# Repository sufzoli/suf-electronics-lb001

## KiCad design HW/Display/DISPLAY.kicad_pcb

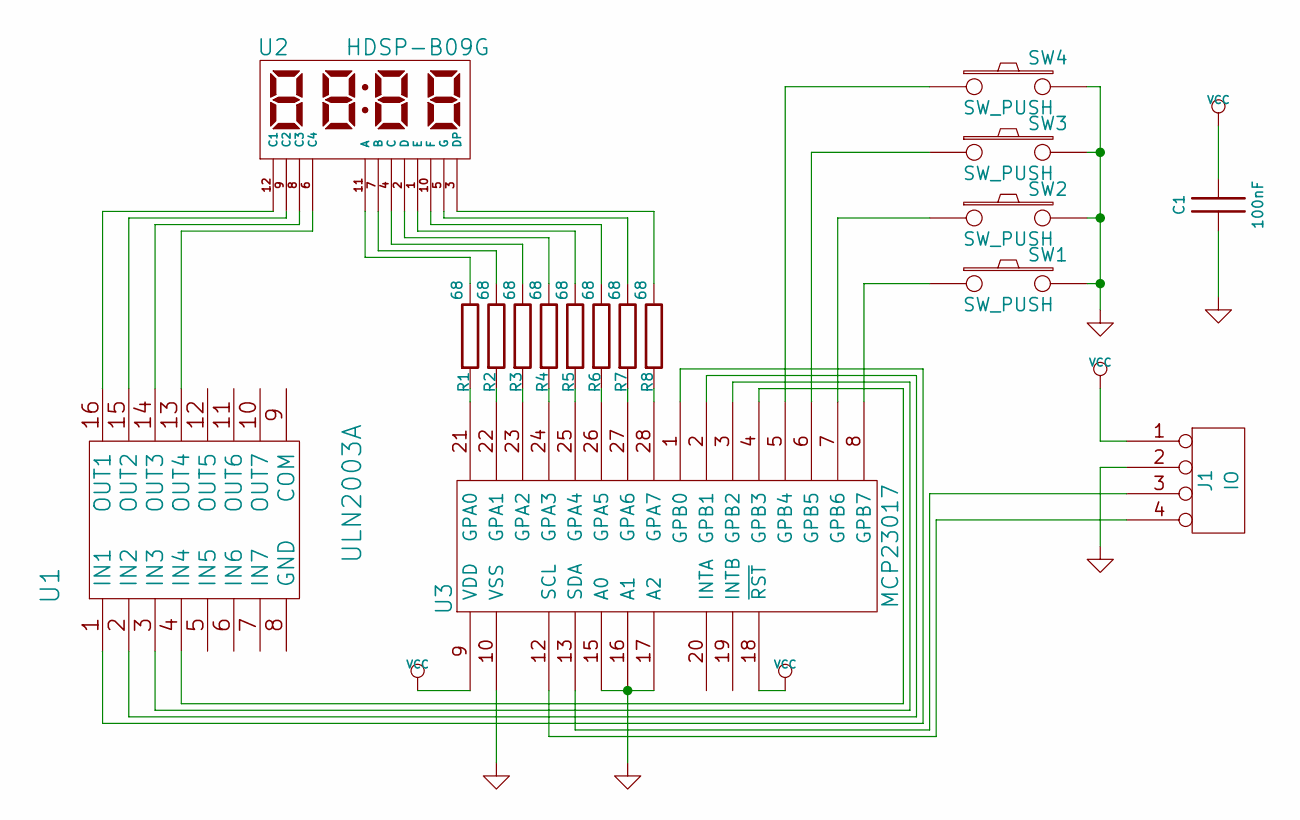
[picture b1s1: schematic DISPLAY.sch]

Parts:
C1: 100nF; C1
J1: IO; HDR-4
R1, R2, R3, R4, R5, R6, R7, R8: 68; R4
SW1, SW2, SW3, SW4: SW_PUSH; SW_PUSH_SMALL
U1: ULN2003A; DIP-16__300
U2: HDSP-B09G; HDSP-B0XG
U3: MCP23017; DIP-28__300

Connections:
GND: C1.2, J1.2, SW1.2, SW2.2, SW3.2, SW4.2, U3.10 (VSS), U3.15 (A0), U3.16 (A1), U3.17 (A2)
unnamed: J1.3, U3.13 (SDA)
unnamed: J1.4, U3.12 (SCL)
unnamed: R1.1, U2.11 (A)
unnamed: R1.2, U3.21 (GPA0)
unnamed: R2.1, U2.7 (B)
unnamed: R2.2, U3.22 (GPA1)
unnamed: R3.1, U2.4 (C)
unnamed: R3.2, U3.23 (GPA2)
unnamed: R4.1, U2.2 (D)
unnamed: R4.2, U3.24 (GPA3)
unnamed: R5.1, U2.1 (E)
unnamed: R5.2, U3.25 (GPA4)
unnamed: R6.1, U2.10 (F)
unnamed: R6.2, U3.26 (GPA5)
unnamed: R7.1, U2.5 (G)
unnamed: R7.2, U3.27 (GPA6)
unnamed: R8.1, U2.3 (DP)
unnamed: R8.2, U3.28 (GPA7)
unnamed: SW1.1, U3.8 (GPB7)
unnamed: SW2.1, U3.7 (GPB6)
unnamed: SW3.1, U3.6 (GPB5)
unnamed: SW4.1, U3.5 (GPB4)
unnamed: U1.1 (IN1), U3.1 (GPB0)
unnamed: U1.2 (IN2), U3.2 (GPB1)
unnamed: U1.3 (IN3), U3.3 (GPB2)
unnamed: U1.4 (IN4), U3.4 (GPB3)
unnamed: U1.13 (OUT4), U2.6 (C4)
unnamed: U1.14 (OUT3), U2.8 (C3)
unnamed: U1.15 (OUT2), U2.9 (C2)
unnamed: U1.16 (OUT1), U2.12 (C1)
VCC: C1.1, J1.1, U3.9 (VDD), U3.18 (~RST)

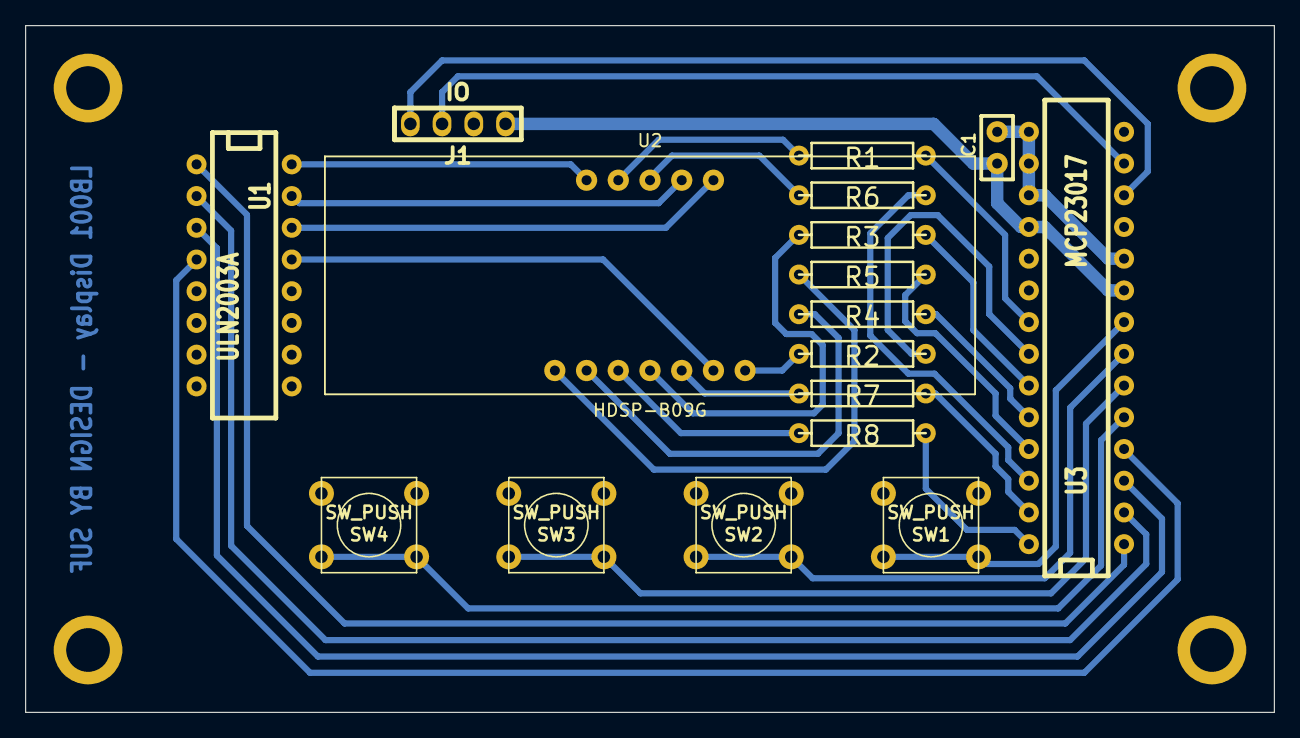
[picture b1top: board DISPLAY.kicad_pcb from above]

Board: 2 copper layers, 100.0 x 55.0 mm, 21 parts (0 on the bottom side), 32 nets.

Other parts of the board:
MNT_HOLE_3.5, MNT_HOLE_3.5#2, MNT_HOLE_3.5#3, MNT_HOLE_3.5#4: MNT_HOLE_3.5

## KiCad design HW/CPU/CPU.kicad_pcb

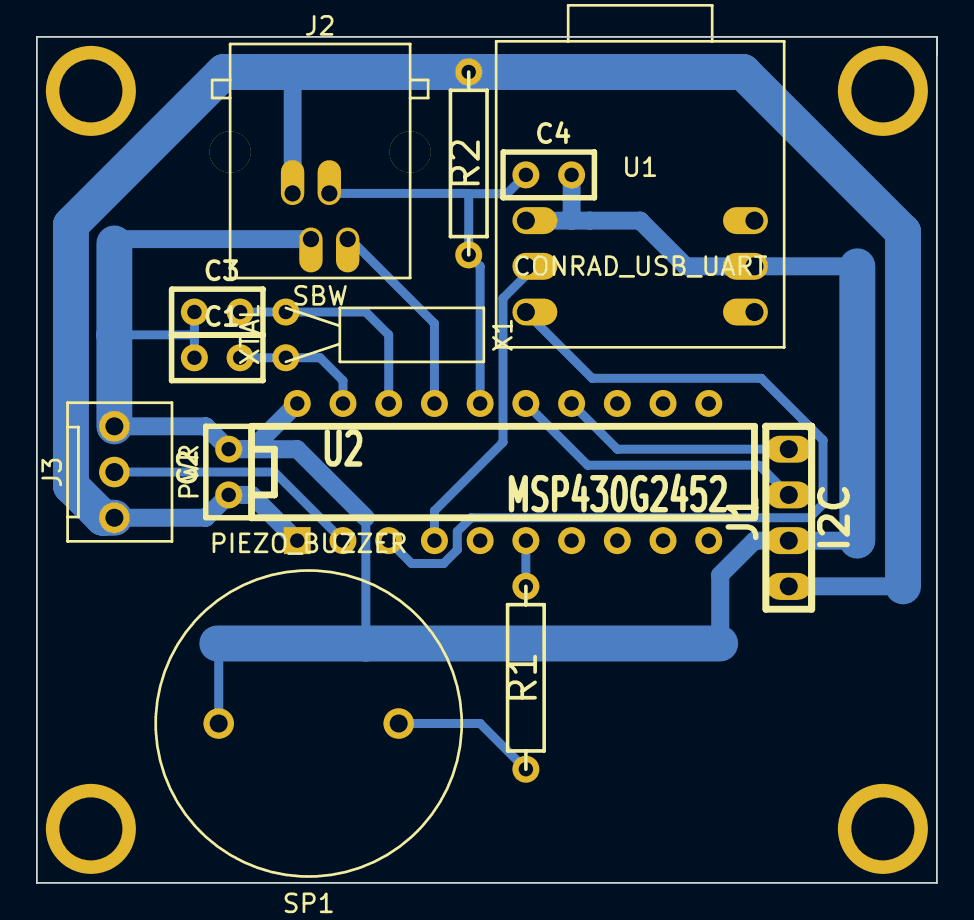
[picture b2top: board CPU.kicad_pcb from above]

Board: 2 copper layers, 50.0 x 47.0 mm, 17 parts (0 on the bottom side), 13 nets.

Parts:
C1, C3: 12pF; C1
C2: 100nF; C1
C4: 1nF; C1
J1: I2C; HDR-4
J2: SBW; SY011M4P4C
J3: PWR; CONN_NCW254-03S
MNT_HOLE_3.5S, MNT_HOLE_3.5S#2, MNT_HOLE_3.5S#3, MNT_HOLE_3.5S#4: Val**; MNT_HOLE_3.5S
R1: 1k; R4
R2: 47k; R4
SP1: PIEZO_BUZZER; PIEZO_BUZZER_D17
U1: CONRAD_USB_UART
U2: MSP430G2452; DIP-20__300LP
X1: XTAL; XTAL_KHZ

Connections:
GND: C1.1, C2.2, C3.1, C4.2, J1.2, J2.2, J3.3, SP1.2, U1.1, U1.5, U2.20
unnamed: J3.2, U2.2
unnamed: J2.4, U2.17
unnamed: R1.2, SP1.1
unnamed: R1.1, U2.6
unnamed: J1.3, U2.15
unnamed: J1.4, U2.14
unnamed: U1.3, U2.3
unnamed: U1.2, U2.4
unnamed: C1.2, U2.19, X1.2
unnamed: C3.2, U2.18, X1.1
unnamed: C4.1, J2.3, R2.2, U2.16
VCC: C2.1, J1.1, J2.1, J3.1, R2.1, U2.1

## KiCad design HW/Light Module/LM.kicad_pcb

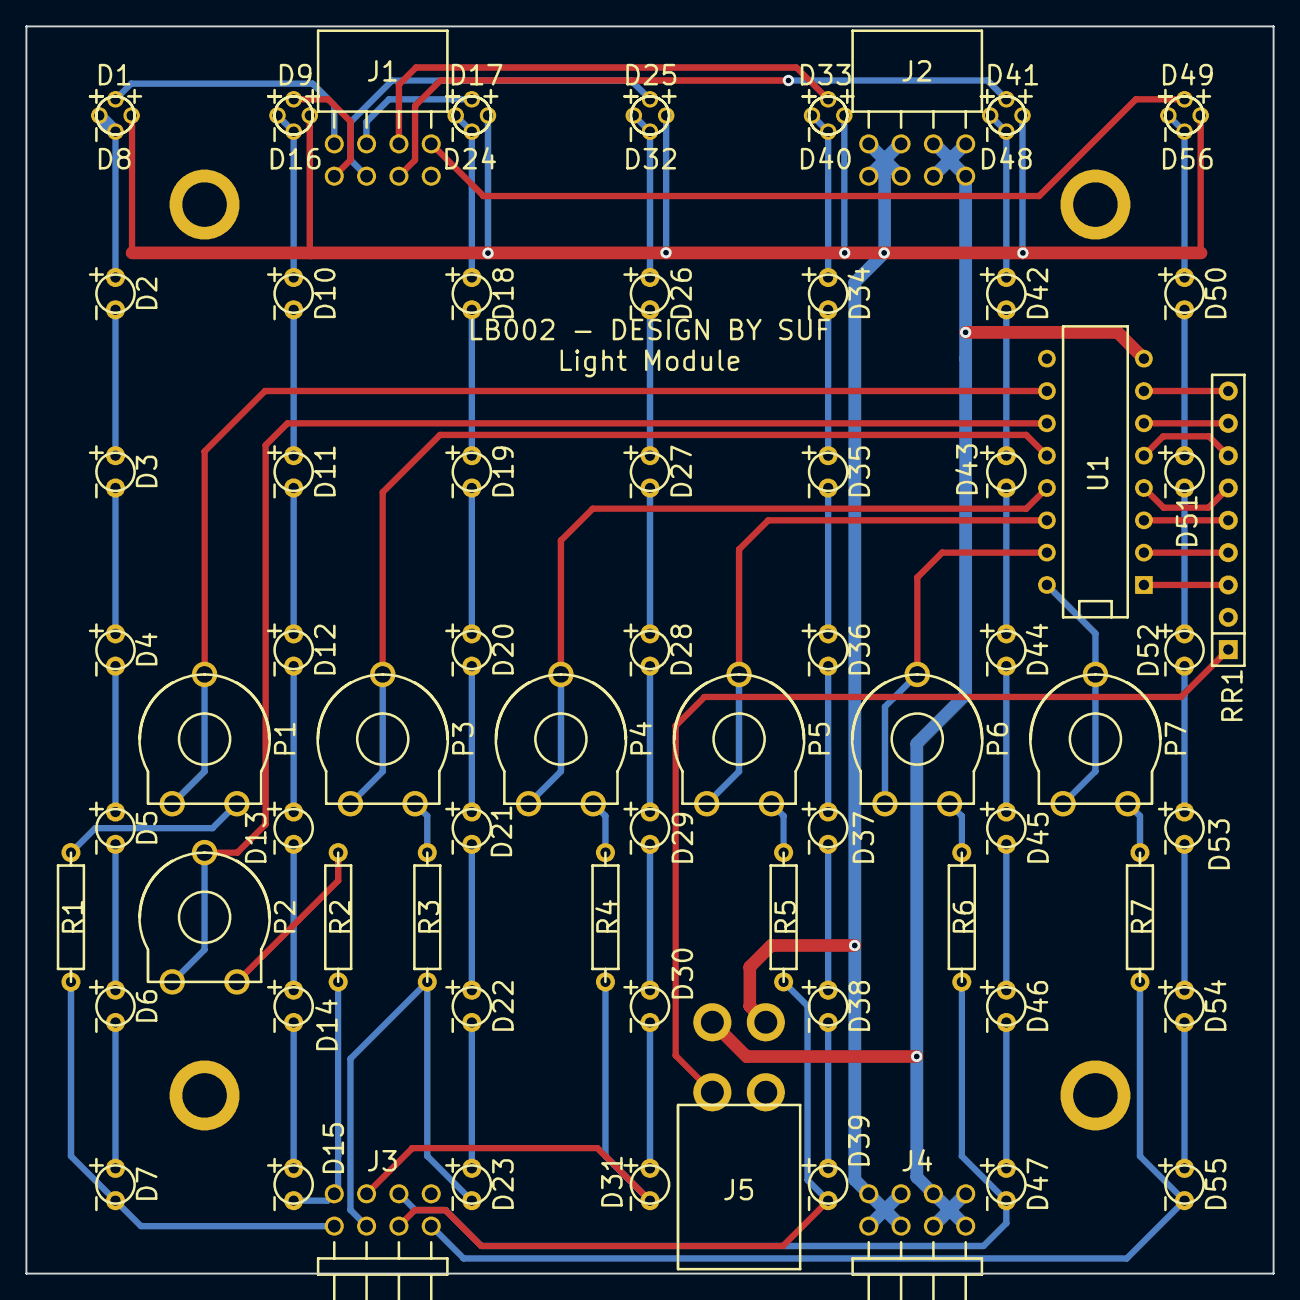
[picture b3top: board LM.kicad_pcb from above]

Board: 2 copper layers, 98.0 x 98.0 mm, 81 parts (0 on the bottom side), 80 nets.

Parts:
D1, D8, D9, D16, D17, D24, D25, D32, D33, D40, D41, D48, D49, D56: LED; LED3-SMALL
D2, D3, D4, D5, D6, D7, D10, D11, D12, D13, D14, D15, D18, D19, D20, D21, D22, D23, D26, D27, D28, D29, D30, D31, D34, D35, D36, D37, D38, D39, D42, D43, D44, D45, D46, D47, D50, D51, D52, D53, D54, D55: LED; LED3
J1, J2: CONN_8; HDR-4x2-90F
J3, J4: CONN_8; HDR-4x2-90M
J5: CONN_4; MINIFIT-2x2-90M
MNT_HOLE_3.5, MNT_HOLE_3.5#2, MNT_HOLE_3.5#3, MNT_HOLE_3.5#4: MNT_HOLE_3.5
P1, P2, P3, P4, P5, P6, P7: VR; VR-1
R1, R2, R3, R4, R5, R6, R7: R; R4
RR1: RR8; SIL-9
U1: ULN2003A; DIP-16__300

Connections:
+48V: D8.1, D16.1, D24.1, D32.1, D40.1, D48.1, D56.1, J2.1, J2.2, J2.3, J2.4, J4.1, J4.2, J4.3, J4.4, J5.3
GND: J2.5, J2.6, J2.7, J2.8, J4.5, J4.6, J4.7, J4.8, J5.1, U1.8
unnamed: D15.2, J3.2, R2.1
unnamed: D47.2, J3.6, R6.1
unnamed: D39.2, J3.5, R5.1
unnamed: D31.2, J3.4, R4.1
unnamed: D23.2, J3.3, R3.1
unnamed: D49.1, J1.7
unnamed: D41.1, J1.6
unnamed: D33.1, J1.5
unnamed: D25.1, J1.4
unnamed: P4.1, P4.2, U1.13
unnamed: P5.1, P5.2, U1.14
unnamed: P6.1, P6.2, U1.15
unnamed: P7.1, P7.2, U1.16
unnamed: D55.2, J3.7, R7.1
unnamed: D28.2, D29.1
unnamed: D38.2, D39.1
unnamed: D37.2, D38.1
unnamed: D36.2, D37.1
unnamed: D35.2, D36.1
unnamed: D34.2, D35.1
unnamed: D33.2, D34.1, D40.2
unnamed: P4.3, R4.2
unnamed: D30.2, D31.1
unnamed: D29.2, D30.1
unnamed: P5.3, R5.2
unnamed: D27.2, D28.1
unnamed: D26.2, D27.1
unnamed: D25.2, D26.1, D32.2
unnamed: P3.3, R3.2
unnamed: P3.1, P3.2, U1.12
unnamed: D22.2, D23.1
unnamed: D21.2, D22.1
unnamed: D20.2, D21.1
unnamed: D19.2, D20.1
unnamed: D51.2, D52.1
unnamed: D17.1, J1.3
unnamed: D9.1, J1.2
unnamed: P7.3, R7.2
unnamed: D54.2, D55.1
unnamed: D53.2, D54.1
unnamed: D52.2, D53.1
unnamed: D50.2, D51.1
unnamed: D49.2, D50.1, D56.2
unnamed: P6.3, R6.2
unnamed: D46.2, D47.1
unnamed: D45.2, D46.1
unnamed: D44.2, D45.1
unnamed: D43.2, D44.1
unnamed: D42.2, D43.1
unnamed: D41.2, D42.1, D48.2
unnamed: D1.1, J1.1
unnamed: RR1.5, U1.3
unnamed: J5.2, RR1.1
unnamed: RR1.9, U1.7
unnamed: RR1.8, U1.6
unnamed: RR1.7, U1.5
unnamed: RR1.6, U1.4
unnamed: RR1.4, U1.2
unnamed: RR1.3, U1.1
unnamed: D7.2, J3.1, R1.1
unnamed: D18.2, D19.1
unnamed: P1.1, P1.2, U1.10
unnamed: P1.3, R1.2
unnamed: D6.2, D7.1
unnamed: D9.2, D10.1, D16.2
unnamed: D5.2, D6.1
unnamed: D4.2, D5.1
unnamed: D3.2, D4.1
unnamed: D2.2, D3.1
unnamed: D1.2, D2.1, D8.2
unnamed: D17.2, D18.1, D24.2
unnamed: P2.1, P2.2, U1.11
unnamed: P2.3, R2.2
unnamed: D14.2, D15.1
unnamed: D13.2, D14.1
unnamed: D12.2, D13.1
unnamed: D11.2, D12.1
unnamed: D10.2, D11.1

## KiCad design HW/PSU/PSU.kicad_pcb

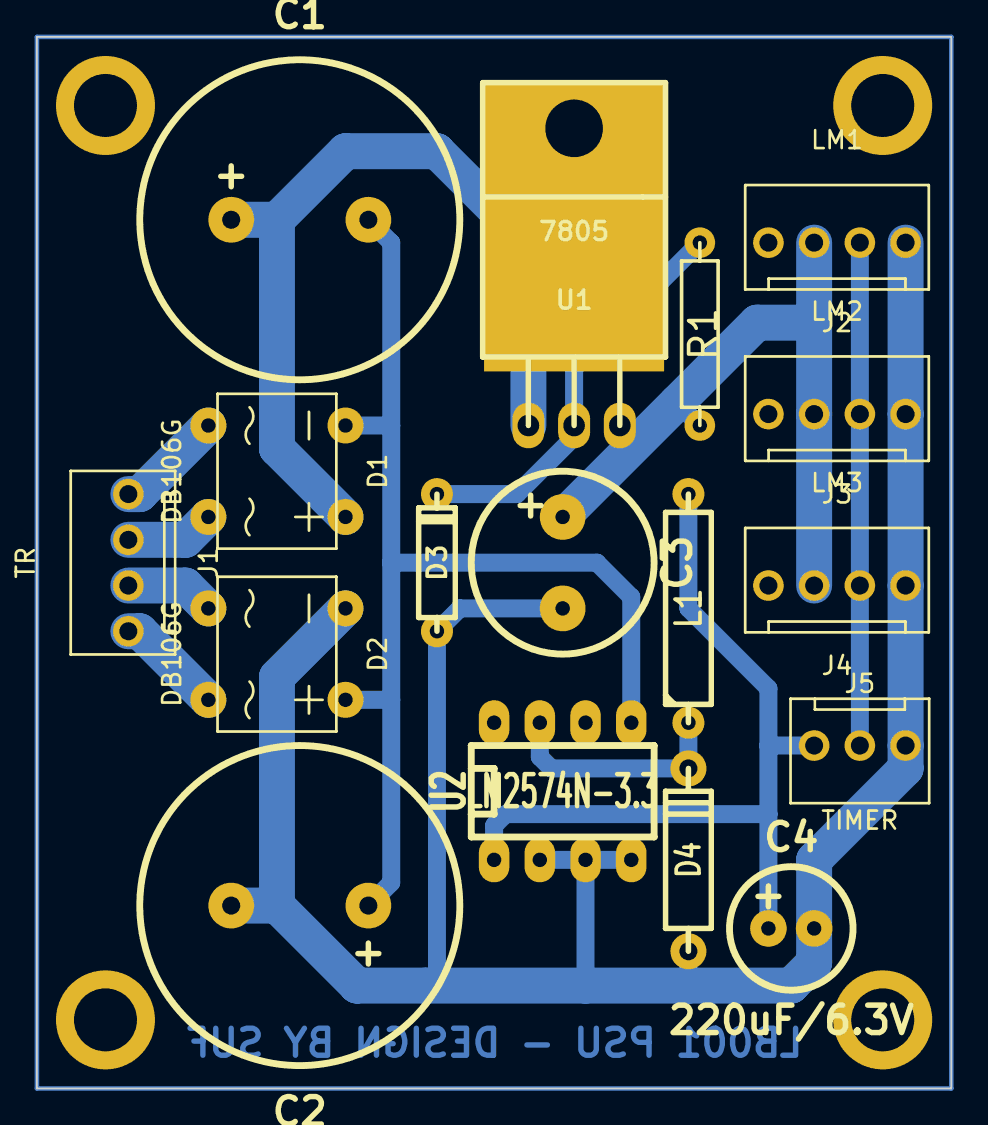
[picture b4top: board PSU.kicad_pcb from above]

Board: 2 copper layers, 50.8 x 58.4 mm, 21 parts (0 on the bottom side), 12 nets.

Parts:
C1, C2: 1000uF/35V; C3P_D7
C3: 22uF/63V; C2P_D4
C4: 220uF/6.3V; C1P_D2.7
D1, D2: DB106G; DB-4
D3: 1N5260B (43V); D3
D4: 1N5819; D4
J1: TR; CONN_NCW254-04S
J2: LM1; CONN_NCW254-04S
J3: LM2; CONN_NCW254-04S
J4: LM3; CONN_NCW254-04S
J5: TIMER; CONN_NCW254-03S
L1: 330uH; R5
MNT_HOLE_3.5, MNT_HOLE_3.5#2, MNT_HOLE_3.5#3, MNT_HOLE_3.5#4: MNT_HOLE_3.5
R1: 2,2K; R4
U1: 7805; TO220
U2: LM2574N-3.3; DIP-8

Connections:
unnamed: D2.2, J1.3
unnamed: D1.3, J1.2
unnamed: D3.2, R1.2, U1.2
unnamed: J2.2, J3.2, J4.2, J5.2
unnamed: C3.1, J2.3, J3.3, J4.3, R1.1, U1.3
unnamed: C1.1, D1.4, U1.1
unnamed: C2.2, C3.2, C4.2, D2.1, D3.1, D4.1, J2.1, J3.1, J4.1, J5.3, U2.2, U2.3, U2.4
unnamed: D2.3, J1.4
unnamed: D1.2, J1.1
unnamed: C4.1, J5.1, L1.2, U2.1
unnamed: D4.2, L1.1, U2.7
unnamed: C1.2, C2.1, D1.1, D2.4, U2.5

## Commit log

2013-12-21 Initial commit Contains: - PSU design - Display design - Light module design - Basic counter software on MSP430G2452
2013-12-21 Software: DCOCLK/SMCLK set to 12MHz The USI I2C clock set to SMCLK/128 - Not using TimerA
2013-12-22 Software: systime.c cleanup from this point the TimerA completely freed up
2013-12-22 Software Basic serial communication added: Displays a ready message and the count value real time
2013-12-23 Software: menu.c/menu.h added - just prints out the button configuration now
2013-12-28 Software Added: - Beep control - Load switching - Backspace handling (not working)
2013-12-30 Software: - menu.c: plus menu text added, minute display added to the start function, flash invalidation added (not tested, not used yet) - serial.h: baud rate changed from 9600 to 115200 (works with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
2014-01-02 Software: - Reorganized the button vector handling - Added a central code config.h - Added additional main menu items (not working)
2014-01-05 Software changes: - menu.c reorganized: context switch block changed to ifs menu entry plug-in handling added save settings to flash added - flash.c all flash handling functions added and tested
2014-01-09 Hardware: Bug fix - PSU library/modul path fixed CPU schematic/pcb design added
2014-01-23 CPU board: PCB Design improvement (incomplette)
2014-01-23 CPU board space optimization
2014-01-24 CPU board: Home PCB print design added
2014-01-27 CPU/CPU_panelize.kicad_pcb error correction
2014-02-21 No Change
2014-03-17 LED Blink C software added
2014-08-14 3D design parts added
2021-03-20 Add Display design
